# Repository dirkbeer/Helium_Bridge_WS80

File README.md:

# Helium_Bridge_WS80

### Note: This is a specialized version of Helium Bridge for the Ecowitt/Fine Ofsset WS-80 Weather Station. It includes data processing and sleep features to optimize for low-power off-grid use. See the [Helium-Bridge](https://github.com/dirkbeer/Helium-Bridge) repository for the more universal Bridge that can bridge multiple sensors. The PCB design provided there works for both.

This repository contains Helium_Bridge_WS80, an application that bridges sensor signals from industrial, scientific, and medical (ISM) devices to the Helium LoRaWAN network. The code is currently based on https://github.com/lnlp/LMIC-node with additional libraries and code to receive, process, and uplink ISM band data to Helium.

The current code and Helium Bridge hardware receives and uplinks data packets from Ecowitt WS80 weather stations. The WS80 transmits FSK-encoded signals in the sub-1GHz ISM bands (915MHz for US versions). This hardware and code receives, averages, and uplinks WS80 data to Helium.

The Helium Bridge software and PCB design was sponsored by an innovation grant from the [Helium Foundation](https://www.helium.foundation/) to be made available open source. This work is freely available for use under its [MIT License](https://github.com/dirkbeer/Helium-Bridge/blob/main/LICENSE), copyright (c) 2023 Dirk Beer and [Gristle King, Inc](https://gristleking.com/). 

The hardware used includes:

* LILYGO® TTGO LoRa32 V2.1_1.6 https://www.lilygo.cc/products/lora3
* CC1101 433MHz Green Tranceiver Module https://www.ebay.com/itm/311955775989?var=610749871056
* MakerFocus 3.7V Lithium Rechargeable Battery w/ JST1.25 Connector 2pin & Protection Board https://www.amazon.com/gp/product/B07CXNQ3ZR
* Treedix 5V 150mA Polysilicon Solar Panel https://www.amazon.com/gp/product/B0831CMJB9
* uxcell 5-Pin Micro USB Type B Male Connector https://www.amazon.com/gp/product/B014GMP4E4
* Protoboard, pin connectors and sockets, wire

Notes: 
* We used the 433MHz CC1101 module because it has sufficient range to the WS80 (~10m) even when operated at 915MHz, and has much easier-to-use pin connectors than the other available modules.
* The 5V solar panel is connected directly to the LoRa32 boards mirco USB port. Voltage should not exceed 5.8V (maximum for VBUS on the CP2104 chip).
* The https://github.com/merbanan/rtl_433 repository has information on decoding WS80 data packets (and those from many other devices). 

The Helium Bridge in action, data displayed using Uplink Engine (https://uplinkengine.com/) on MeteoScientific (https://meteoscientific.com/).

How to build the hardware:
* TBD

How to run the software:
* TBD. For now, see the original LMIC-node Readme below.

Josef de Beer at SDHGPA wrote much of the code used to receive and process WS80 packets using the TI CC1101 module. 

Copyright (c) 2023 Dirk Beer and Gristle King Inc

---
---
# LMIC-node

One example to rule them all

## Contents

- [1 Introduction](#1-introduction)
  - [1.1 What does it do?](#11-what-does-it-do)
  - [1.2 Implemented features](#12-implemented-features)
  - [1.3 Requirements](#13-requirements)
- [2 Supported Boards](#2-supported-boards)
  - [2.1 LoRa development boards](#21-lora-development-boards)
  - [2.2 Development boards with external SPI LoRa module](#22-development-boards-with-external-spi-lora-module)
- [3 Details](#3-details)
  - [3.1 setup() function](#31-setup-function)
  - [3.2 doWork job](#32-dowork-job)
  - [3.3 processWork() function](#33-processwork-function)
  - [3.4 processDownlink() function](#34-processdownlink-function)
  - [3.5 Uplink messages](#35-uplink-messages)
  - [3.6 Downlink messages](#36-downlink-messages)
    - [3.6.1  Reset-counter downlink command](#361--reset-counter-downlink-command)
  - [3.7 Status information](#37-status-information)
    - [3.7.1 Serial port and display](#371-serial-port-and-display)
    - [3.7.2 LED](#372-led)
  - [3.8 User modifiable code](#38-user-modifiable-code)
  - [3.9 Board-id](#39-board-id)
  - [3.10 Device-id](#310-device-id)
  - [3.11 platformio.ini](#311-platformioini)
  - [3.12 lorawan-keys.h](#312-lorawan-keysh)
  - [3.13 Board Support Files (BSF)](#313-board-support-files-bsf)
  - [3.14 Payload formatters](#314-payload-formatters)
    - [3.14.1 Uplink decoder](#3141-uplink-decoder)
  - [3.15 External libraries](#315-external-libraries)
- [4 Settings](#4-settings)
  - [4.1 Board selection](#41-board-selection)
  - [4.2 Common settings](#42-common-settings)
  - [4.3 LoRaWAN library settings](#43-lorawan-library-settings)
    - [4.3.1 MCCI LoRaWAN LMIC library settings](#431-mcci-lorawan-lmic-library-settings)
    - [4.3.2 IBM LMIC framework settings](#432-ibm-lmic-framework-settings)
  - [4.4 Board specific settings](#44-board-specific-settings)
  - [4.5 Board Support Files](#45-board-support-files)
- [5 Instructions](#5-instructions)
  - [5.1 Select your board](#51-select-your-board)
  - [5.2 Select your LoRaWAN region](#52-select-your-lorawan-region)
  - [5.3 Provide the LoRaWAN keys for your node](#53-provide-the-lorawan-keys-for-your-node)
  - [5.4 Compile and upload](#54-compile-and-upload)
  - [5.5 Add uplink decoder function in TTN Console](#55-add-uplink-decoder-function-in-ttn-console)
- [6 Additional information](#6-additional-information)
  - [6.1 Pinout diagrams](#61-pinout-diagrams)
  - [6.2 The Things Network Forum](#62-the-things-network-forum)
  - [6.3 Not yet tested](#63-not-yet-tested)
  - [6.4 Known issues](#64-known-issues)
- [7 Tips](#7-tips)
  - [7.1 Serial Monitor](#71-serial-monitor)
  - [7.2 Antenna](#72-antenna)
  - [7.3 Distance to gateway](#73-distance-to-gateway)
- [8 Example output](#8-example-output)
  - [8.1 Serial Monitor](#81-serial-monitor)
  - [8.2 Display](#82-display)
- [9 Release History](#9-release-history)

## 1 Introduction

LMIC-node is an example LoRaWAN application for a node that can be used with [The Things Network](https://www.thethingsnetwork.org/). It demonstrates how to send uplink messages,  how to receive downlink messages, how to implement a downlink command and it provides useful status information. With LMIC-node it is easy to get a working node quickly up and running. LMIC-node supports many popular (LoRa) development boards out of the box. It uses the Arduino framework, the LMIC LoRaWAN library and PlatformIO.

Basic steps to get a node up and running with LMIC-node:

- Select a supported board in `platformio.ini`.
- Select your LoRaWAN region in `platformio.ini`.
- Provide the LoRaWAN keys for your node (end device) in `lorawan-keys.h`.
- Compile and upload the firmware and you're ready to go!

### 1.1 What does it do?

- During startup LMIC-node sends some information to the serial port (if enabled) and display (if present and enabled). If OTAA activation is used LMIC-node will explicitly start a join to setup a network session.
- The main work like collecting input data and scheduling uplink messages is performed in the doWork job. This job runs at regular intervals (`DO_WORK_INTERVAL_SECONDS`).
- LMIC-node uses a counter to simulate a real sensor. The counter gets automatically incremented each time its value is read. The counter value is read by the doWork job and then transmitted via an uplink message to The Things Network (TTN).
- In addition LMIC-node also implements a downlink command to reset the counter. The command is sent to the node via a downlink message. When the 'reset counter' command is received by the node it will reset the counter value.
- While all this is happening LMIC-node outputs status information to the serial port for viewing on the serial monitor and also outputs information to the display (if present). The status information will show time, events (e.g. EV_JOINED, EV_TXCOMPLETE), uplink and downlink framecounters, RSSI and SNR of received downlink messages and when a downlink contains data the data will be displayed as bytes.
- The uplink messages can be viewed in the TTN Console. It is also possible to send the 'reset counter' downlink message from the console to the node. The effect of resetting the counter can be watched on the console as arriving uplink messages will show the new counter value.  

Once the node is up and running you can start to explore and customize the source code to your own needs, e.g. add support for sensors. It is always easier to start with something that already works and then continue from there. Have fun!

### 1.2 Implemented features

- Send uplink messages.
- Receive downlink messages.
- Implements a downlink command.
- Provide detailed status feedback via serial port, LED and OLED display.  
*Each of these output channels can be separately enabled/disabled (e.g. to save memory or power).*
- Supports both OTAA and ABP activation. Simply switch via configuration option.
- LoRaWAN keys are placed in a separate file: `lorawan-keys.h`.
  - Protection against accidentally uploading LoRaWAN keys to public Git(Hub) repositories.
  - Easy to swap LoRaWAN keys for testing or for use with multiple devices.
- Requires only some configuration, but no programming or modification of source code to get it up and running.
- Configuration is done in a single project configuration file: `platformio.ini`.
- User modifiable code is clearly marked in the source code.
- Supports two different LMIC libraries: MCCI LoRaWAN LMIC library and IBM LMIC framework.
- Support for many popular (LoRa) development boards.
- Cross-platform, tested on STM32, SAMD21, ESP32, ESP8266, RP2040, MKL26Z64VFT4, ATmega32u4 and ATmega328 boards.
- Hardware dependencies are handled in separate Board Support Files (BSF).
- Built-in 'wait for serial port ready' with adjustable timeout and countdown visible on display. *Useful when using the serial monitor with boards with MCU with integrated USB support.*
- Abstraction of the serial port so code can print to `serial` without needing to know if it must print to `Serial` or `SerialUSB`.
- Use correct GPIO pins for onboard LED, display, LoRa hardware, I2C and SPI ports even if these are incorrectly defined in the BSP.
- Avoid hardware conflicts i.e. GPIO's shared between onboard LED, I2C, SPI and/or Vext.
- Explicitly initialize I2C and SPI interfaces with correct pins if default pins are incorrectly defined in the BSP.
- Select the proper subband for regions US915 and AU915.
- For LMIC debugging, for each board, LMIC_PRINTF_TO is defined for the correct serial port.
*No need to set the `LMIC_PRINTF_TO` parameter to `Serial` or `SerialUSB` manually.*

### 1.3 Requirements

The following is required to use LMIC-node:

- **A supported** LoRa **development board** or development board with external Semtech SX127*x*, HopeRF RFM9*x* or HPDTek HPD1*x*A SPI LoRa module.
- **A computer with [PlatformIO](https://platformio.org/) installed**. PlatformIO is used instead of Arduino IDE because more flexible, more powerful and it better supports cross-platform development. For installation see [PlatformIO installation instructions](https://docs.platformio.org/en/latest/integration/ide/vscode.html).
- **Internet connection**. PlatformIO will automatically download and install packages (Arduino cores, toolchains and libraries) as needed.  
If PlatformIO is freshly installed the downloading may take some time. Once installed it will be possible to work offline.
- **USB cable**. For boards without onboard USB also a **USB to serial adapter** is needed (for STM32 optionally a STLink programmer).
- **Wiring**: Some LoRa development boards require manual wiring of LoRa DIO1 (see table below). When using a development board with external LoRa module then everything must be manually wired. For wiring details see the board's Board Support File (BSF).
- **Node registration**: A node (end device) must be created/registered in The Things Network (TTN) Console before it can be used. The LoRaWAN keys for the device must be copied from the TTN Console to file `lorawan-keys.h`. Registration is not further described here. For more information see [The Things Network documentation](https://www.thethingsnetwork.org/docs/index.html), [The Things Stack documentation](https://www.thethingsindustries.com/docs) and [The Things Network Forum](https://www.thethingsnetwork.org/forum/).
- **Skills**: You should already be familiar with compiling and uploading basic Arduino sketches to your board and how to use a serial monitor.

**Display**:  
LMIC-node supports the following display type: SSD1306 128x64 I2C OLED. These are the displays used on Heltec Wifi LoRa 32 and TTGO LoRa32 boards. When connecting an external display use this type. Use of other I2C displays is possible but requires modification of LMIC-node which is not further described here.

Not yet a requirement but this document assumes that you will be using The Things Network V3 as The Things Network V2 will cease operation by the end of 2021 and should not be used for new development.

## 2 Supported Boards

The following tables list the boards currently supported by LMIC-node.

Explanation of columns: MCU: microcontroller. Wiring required: yes means manual wiring of DIO1 is required. USB: has onboard USB. LED: yes: has onboard LED *and* is usable (no hardware conflicts). Display: yes means has onboard display. Board-id: board identifier as used by LMIC-node.

### 2.1 LoRa development boards

The following LoRa development boards have onboard LoRa support. Most have onboard USB that supports automatic firmware upload and serial over USB for serial monitoring. Some boards require manual wiring of the LoRa DIO1 port. For boards without onboard display an external display can be optionally connected. For details and wiring instructions see the board's BSF.

| Board name                        | MCU               | Wiring required | USB      | LED      | Display   | Board-id |
| ----------                        | ---               | ---             | ---      | ---      | ---       | --- |  
| Adafruit Feather M0 RFMx LoRa     | SAMD21G18         | yes _\*1_       | yes      | yes      | no        | adafruit_feather_m0_lora |
| ST B-L072Z-LRWAN1 Discovery kit   | STM32L072CZ       | no              | yes      | yes      | no        | discovery_l072z_lrwan1 |
| Heltec WiFi LoRa 32 V2            | ESP32             | no              | yes      | yes      | yes       | heltec_wifilora32_v2 |
| Heltec WiFi LoRa 32 (1.x)         | ESP32             | no              | yes      | yes      | yes       | heltec_wifilora32 |
| Heltec Wireless Stick             | ESP32             | no              | yes      | yes      | yes _\*7_ | heltec_wireless_stick |
| Heltec Wireless Stick Lite        | ESP32             | no              | yes      | yes      | no        | heltec_wireless_stick_lite |
| Pycom LoPy4                       | ESP32             | no              | no _\*4_ | no _\*5_ | no        | lopy4 |
| BSFrance LoRa32u4 II<br>*versions v1.0, v1.1, v1.2 and v1.3* | ATmega32u4 | yes _\*2_ | yes | yes | no    | lora32u4II |
| TTGO LoRa32 V1.3                  | ESP32             | no              | yes      | no       | yes       | ttgo_lora32_v1 |
| TTGO LoRa32 V2.0                  | ESP32             | yes _\*3_       | yes      | no _\*6_ | yes       | ttgo_lora32_v2 |
| TTGO LoRa32 V2.1.6                | ESP32             | no              | yes      | no       | yes       | ttgo_lora32_v21 |
| TTGO T-Beam<br>*versions v0.5, v0.6 and v0.7* | ESP32 | no              | yes      | yes      | no        | ttgo_tbeam |
| TTGO T-Beam<br>*versions v1.0 and v1.1*       | ESP32 | no              | yes      | no       | no        | ttgo_tbeam_v1 |

_\*1_: DIO1 must be manually wired to GPIO6.  
_\*2_: For versions 1.0, 1.1 and 1.2 DIO1 must be manually wired to GPIO5 (version 1.3 is already wired on the PCB).  
_\*3_: DIO1 must be manually wired to GPIO33.  
_\*4_: Requires USB to Serial adapter or Pycom Expansion Board which is explained further below.  
_\*5_: Has onboard Neopixel RGB LED but is currently not supported by LMIC-node.  
_\*6_: Either display (I2C) or LED can be used but not both at the same time. LED is default disabled.  
_\*7_: Display (64x32) not supported by LMIC-node because resolution is too small.

### 2.2 Development boards with external SPI LoRa module

The following development boards require an external Semtech SX127*x*, HopeRF RFM9*x* or HPDTek HPD1*x*A SPI LoRa module *(Semtech SX1262 is currently not supported by the LMIC library)*.
Most boards have onboard USB that supports automatic firmware upload and serial over USB for serial monitoring.
An external display can be optionally connected. For details and wiring instructions see the board's BSF.

| Board name                        | MCU            | Wiring required | USB       | LED      | Display | Board-id |
| ----------                        | ---            | ---             | ---       | ---      | ---     | -------- |
| Adafruit QT PY                    | SAMD21E18      | yes             | yes       | no _\*5_ | no      | adafruit_qt_py_m0 |
| Black Pill STM32F103C8 128k       | STM32F103C8T6  | yes             | yes _\*8_ | yes      | no      | blackpill_f103c8_128k |
| Black Pill STM32F103C8 64k        | STM32F103C8T6  | yes             | yes _\*8_ | yes      | no      | blackill_f103c8 |
| Blue Pill STM32F103C8 128k        | STM32F103C8T6  | yes             | yes _\*8_ | yes      | no      | bluepill_f103c8_128k |
| Blue Pill STM32F103C8 64k         | STM32F103C8T6  | yes             | yes _\*8_ | yes      | no      | bluepill_f103c8 |
| Lolin D32 Pro                     | ESP32          | yes             | yes       | yes      | no      | lolin_d32_pro |
| Lolin D32                         | ESP32          | yes             | yes       | yes      | no      | lolin_d32 |
| Lolin32                           | ESP32          | yes             | yes       | yes      | no      | lolin32 |
| NodeMCU-32S                       | ESP32          | yes             | yes       | yes      | no      | nodemcu_32 |
| NodeMCU V2 (aka v1.0)             | ESP8266        | yes             | yes       | yes      | no      | nodemcuv2 |
| Raspberry Pi Pico                 | RP2040         | yes             | yes       | yes      | no      | pico |
| Arduino Pro Mini (ATmega328 8mHz) | ATmega328      | yes             | yes       | no       | no      | pro8mhzatmega328 |
| SAMD21 M0-Mini                    | SAMD21G18      | yes             | yes       | no       | no      | samd21_m0_mini |
| Teensy LC                         | MKL26Z64VFT4   | yes             | yes       | yes      | no      | teensylc |

_\*5_: Has onboard Neopixel RGB LED but is currently not supported by LMIC-node.  
_\*8_: These boards have onboard USB but by default do not support firmware upload over USB or serial over USB. For upload use a STLink programmer or USB to serial adapter.

## 3 Details

This chapter contains detailed information about LMIC-node.

### 3.1 setup() function

During setup the following components and any corresponding libraries are initialized: serial port, display, LED, LoRa pin mappings, I2C, SPI, LMIC. Additionally other hardware like sensors and their libraries can be initialized (LMIC-node uses a counter to simulate a sensor).

The first step in `setup()` is:

```cpp
// boardInit(InitType::Hardware) must be called at start of setup() before anything else.
bool hardwareInitSucceeded = boardInit(InitType::Hardware);
```

The `boardInit()` function is defined in the board's Board Support File.  
If OTAA activation is used then during setup a join will be explicitly started to establish a connection with the network.  
The last step in `setup()` is scheduling the first run of the `doWork` job.

### 3.2 doWork job

The `doWork` job runs every `DO_WORK_INTERVAL_SECONDS`.  
To run the job the `doWorkCallback()` function is executed by the LMIC scheduler.  
`doWorkCallback()` calls the `processWork()` function where the actual work is performed.  
The first `doWork` run is started in `setup()`. On completion `doWork` reschedules itself for the next run.

When the node has joined and the `EV_JOINED` event is handled by the event handler, the next scheduled doWork job is cancelled and is re-scheduled for immediate execution. This is done to prevent that any uplink will have to wait until the current doWork interval ends. `processWork()` skips doing any work while the node is still joining. As a result sending the first uplink message may have to wait until the current doWork interval ends (max `DO_WORK_INTERVAL_SECONDS` seconds). Directly running the doWork job after a join prevents the in this case unnecessary and unwanted delay.

### 3.3 processWork() function

The `processWork()` function contains user code that performs the actual work like reading sensor data and scheduling uplink messages. In LMIC-node `processWork()` will skip doing any work if the node is still joining for two reasons:

1. To prevent unnecessary incrementing of the counter.
2. Uplink messages cannot yet be sent.

### 3.4 processDownlink() function

The `processDownlink()` function contains user code for processing a downlink message.  
`processDownlink()` is called from the event handler function when an EV_TXCOMPLETE event is handled and a downlink message was received.

### 3.5 Uplink messages

The counter is implemented as an unsigned 16 bit integer.
The uplink payload consists of the counter value, 2 bytes in msb format (most significant byte first).
The frame port number used for uplink messages is 10.
Port 10 is used to demonstrate that other port numbers than the default 1 can be used.

### 3.6 Downlink messages

There are two types of downlink messages. Downlink messages containing user data and downlink messages containing MAC commands. MAC commands are sent by the network server to set or query network related settings.

When a downlink message is received its RSSI and SNR values will be displayed as well as the port number. If the port number is 0 and no data is shown then a MAC command was received.

If the port number is greater than 0 and user data was received the data will be displayed as a sequence of byte values. Contents of downlink data will only be output to the serial port and not to the display because the display is too small to fit all information on a single screen.

#### 3.6.1  Reset-counter downlink command

The reset-counter downlink uses 100 as frame port number.
The reset command is represented by a single byte with hex value 0xC0 (for Counter 0).
When a downlink message is received on port 100, the length of the data is 1 byte and the value is 0xC0 then the `resetCounter()` function will be called and the counter will be reset to 0. If the received payload data is longer than a single byte then the reset-counter command will not be performed.

### 3.7 Status information

The following status information is shown:

#### 3.7.1 Serial port and display

At the start:

- Timeout countdown value while waiting for serial port to become ready is shown on the display. This value is only shown for boards where `WAITFOR_SERIAL_SECONDS_DEFAULT` is defined in the BSF with a value unequal to 0.

In the header:

- Program title "LMIC-node".
- Device-id.
- Used LMIC library. MCCI or Classic. On display only an asterisk will be shown if Classic is used.
- If OTAA or ABP activation is used. On display only ABP will be shown if used.
- LMIC debug level if > 0. *(on serial port only)*
- DoWork job time interval (DO_WORK_INTERVAL_SECONDS). On display 'interval' label is abbreviated to "I".

When joined:

- Network-id. *(on serial port only, MCCI LMIC only)*
- Device address. *(on serial port only, MCCI LMIC only)*
- Sessions keys *(son erial port only, MCCI LMIC only)*

Continuously:

- During transmission of uplink and downlink messages a transmit symbol will be shown in the top-right of the display. the transmit symbol and LED are called transmit indicators. For MCCI LMIC transmit indicators are set to on while handling the EV_TXSTART event. Classic LMIC does not generate this event however. For Classic LMIC the transmit indicators will be set to on after an uplink has been successfully scheduled (which is less precise).
- A notification when the doWork job is started. *(on serial port only)*
- A notification when input data was collected *(on serial port only)*
- Message with Counter value. On display label is abbreviated to "Ctr".
- A notification "packet queued" when an uplink message is scheduled.
- A notification if a packet cannot be scheduled because transmission or reception of another message is still pending.
- An error message if scheduling of an uplink message failed.
- Events generated by the LMIC library (e.g. EV_JOINED, EV_TXCOMPLETE).
- When event EV_TXCOMPLETE is received the frame counters are printed.
- For each downlink message the following will be shown:
  - Message that downlink was received
  - RSSI and SNR values
  - Frame port number
  - If data was received, length of data
  - If data was received, the data is shown as as byte *(serial port only)*
  - Message if reset-counter command was received *(serial port only*)
- Notification when counter is reset.

For events and notifications a timestamp (`ostime`) will be shown. LMIC uses values of the type ostime_t to represent time in ticks. The rate of these ticks defaults to 32768 ticks per second (but may be configured at compile time to any value between 10000 ticks per second and 64516 ticks per second).

#### 3.7.2 LED

The LED is a transmit indicator similar to the transmit symbol on the display. For a description when the LED is on and off see the description for the transmit symbol above.

### 3.8 User modifiable code

LMIC-node will work out of the box without having to do any programming or modifying of source code. However, LMIC-node will only do a few tricks: Send counter value via uplink messages, handle reset-counter downlink command and show detailed status information.

To make LMIC-node do other, more useful things e.g. reading values from a temperature and humidity sensor or from a water-level sensor and sending these via uplink messages, requires modifying and extending the source code.

Most of the source code is boiler plate code that does not need to be changed.
Code for things like adding support for sensors or implement other downlink commands is called *User Code*. In `LMIC-node.cpp` three sections in the source code are marked as *User Code*. In `platformio.ini` one section is marked for User Code where additional libraries for User Code can be added. Try to put your user code in these sections (this will prevent accidentally messing things up).

If you are aware of what you are doing you are of course free to change every single line of code to your needs, but if this is new to you it might be safer to restrict modifications to the user code sections.

Reading sensors (etc), preparing uplink payload and scheduling an uplink message for transmission can be done in function `processWork()`. Handling of downlink messages and adding your own downlink commands can be done in function `processDownlink()`.

The User Code sections in `LMIC-node.cpp` are marked as follows:

```cpp
//  █ █ █▀▀ █▀▀ █▀▄   █▀▀ █▀█ █▀▄ █▀▀   █▀▄ █▀▀ █▀▀ ▀█▀ █▀█
//  █ █ ▀▀█ █▀▀ █▀▄   █   █ █ █ █ █▀▀   █▀▄ █▀▀ █ █  █  █ █
//  ▀▀▀ ▀▀▀ ▀▀▀ ▀ ▀   ▀▀▀ ▀▀▀ ▀▀  ▀▀▀   ▀▀  ▀▀▀ ▀▀▀ ▀▀▀ ▀ ▀

const uint8_t payloadBufferLength = 4;    // Adjust to fit max payload length

//  █ █ █▀▀ █▀▀ █▀▄   █▀▀ █▀█ █▀▄ █▀▀   █▀▀ █▀█ █▀▄
//  █ █ ▀▀█ █▀▀ █▀▄   █   █ █ █ █ █▀▀   █▀▀ █ █ █ █
//  ▀▀▀ ▀▀▀ ▀▀▀ ▀ ▀   ▀▀▀ ▀▀▀ ▀▀  ▀▀▀   ▀▀▀ ▀ ▀ ▀▀
```

The User code section in `platformio.ini` is marked as follows:

```ini
;   ███ Add additional libraries for User Code below this line ███
```

Names of libraries needed for User Code can be specified below above line.

### 3.9 Board-id

LMIC-node uses a _board-id_ to identify a specific type of board. _board-id_ is similar to PlatformIO's _board_ but latter is limited to BSP's defined in Arduino cores. Unfortunately there does not exist a dedicated BSP for each board supported by LMIC-node. Therefore LMIC-node defines its own board identifiers.

_board-id_ is kept identical or as similar as possible to PlatformIO's _board_. For simplicity and consistency _board-id_ only uses underscores and lowercase characters (e.g. `heltec_wifi_lora_32_v2` and `ttgo_lora32_v2`) while PlatformIO's _board_ uses hyphens, underscores and mixed case characters (e.g. `heltec_wifi_lora_32_V2` and `ttgo-lora32-v2`). Board-id `lora32u4II` is an exception, the `II` is uppercase because it is a Roman numeral.  

 If a proper _board_ definition and BSP for some version of a development board do currently not exist then LMIC-node defines its own board with its own _board-id_. In which case it will use the closest matching _board_ in PlatformIO and add a separate BSF for _board-id_ where the differences can be properly handled. In this case _board-id_ will be the same as _board_ but suffixed with a version e.g. `ttgo_t_beam_v1`. In this example there only exists a board `ttgo-t-beam` in PlatformIO but no `ttgo-t-beam-v1` while there are important hardware differences between v0.x and v1.x versions of these boards.

### 3.10 Device-id

LMIC-node uses a device-id to identify a device. The device-id is used for display purposes in status information that is output to the serial port and display. Device-id's allow different devices to be easily recognized when they have different device-id's, because their device-id is shown on the display (if present) and/or serial monitor (serial port). The length of a device-id should be limited to max 16 characters long, otherwise it will not fit on a display.

When creating a device in the TTN console one must specify a unique device identifier for the device. The device-id used in LMIC-node is only used for display purposes (and is not the same as the device identifier in the TTN Console) but it is useful to use the same device-id for LMIC-node as the device identifier in the TTN console (or at least make it similar). That will make it easier to recognize traffic in the TTN console because the device identifier displayed on the console and the device-id displayed on the node's display (or serial monitor) will match.

In the BSF a default device-id (`DEVICEID_DEFAULT`) is defined per board type. The default device-id can be overriden by defining `DEVICEID` in file `lorawan-keys.h`, or defining `ABP_DEVICEID` in `lorawan-keys.h`. If defined latter will be used when ABP activation is used.

`lorawan-keys.h` can contain both the keys used for OTAA activation as well as the keys used for ABP activation. Keys used for OTAA and ABP are different and they have different names. Only the keys for the used actvation type (OTAA or ABP) need to be specified.

Tip: For testing purposes it is possible to create two different devices in the TTN console for the same hardware device, one for OTAA activation and the other for ABP activation. Both sets of keys can be added to lorawan-keys.h and for both a different device-id can be added to lorawan-keys.h. This way a single hardware device can be used for both OTAA and ABP (only one at a time). All that to needs to be done to switch the device from OTAA to ABP is to enable the `-D ABP_ACTIVATION` setting in the `[common]` section in `platformio.ini` (or vice versa) and then recompile and upload the firmware.

### 3.11 platformio.ini

`platformio.ini` is the project configuration file. This file contains all configuration settings like program options, names of libraries and build options. It contains below sections:

- **[platformio]**  
  Contains a list of board names and their corresponding board-id ('environment definitions').  
  This is used to select a board (by uncommenting the line with the board-id to be selected).

- **[common]**  
  Contains settings used for all boards.

- **[mcci_lmic]**  
  Contains MCCI LoRaWAN LMIC library specific settings.  
  MCCI LoRaWAN LMIC library is used for boards with 32-bit MCU.

- **[classic_lmic]**  
  Contains IBM LMIC framework library specific settings.  
  IBM LMIC framework is used for boards with 8-bit AVR MCU.  
  These boards have less available memory and Classic LMIC uses less memory resources than MCCI LMIC.  
  It is not possible to use LMIC-node with MCCI LMIC on these boards due to insufficient memory.  
**Be aware that Classic LMIC is not fully LoRaWAN compliant and should not be used with ABP activation on The Things Network V3. IBM LMIC framework (Clasic LMIC) was recently deprecated and is not further maintained.**

- **[env:_\<board-id\>_]**  
  Board specific sections (called _Environments_ in PlatformIO terminology). E.g. [env:lolin32]. A board specific section contains settings that are specific for one type of board.   It contain settings like which LMIC library to use and program options like USE_SERIAL, USE_LED and USE_DISPLAY.  

Comments in platformio.ini start with a semicolon ( ; ) character. To uncomment a line  remove the semicolon prefix. To comment a line add a semicolon prefix.

### 3.12 lorawan-keys.h

File `lorawan-keys.h` contains the LoRaWAN keys for a node. The keys are placed in a separate file for:

- Protection against accidentally uploading LoRaWAN keys to public Git(Hub) repositories.
- Prevent that source code needs to be modified for changing keys.
- Make it easy to swap LoRaWAN keys for testing purposes or for use with multiple devices.

The keys use three different formats (lsb, msb and uint32_t). lsb: least significant byte, msb: most significant byte. The TTN console provides options to copy keys in different formats. Use the correct formats as shown in below extract from `lorawan-keys_example.h`:

```cpp
// Optional: If DEVICEID is defined it will be used instead of the default defined in the BSF.
// #define DEVICEID "<deviceid>"

// Keys required for OTAA activation:

// End-device Identifier (u1_t[8]) in lsb format
#define OTAA_DEVEUI 0x00, 0x00, 0x00, 0x00, 0x00, 0x00, 0x00, 0x00

// Application Identifier (u1_t[8]) in lsb format
#define OTAA_APPEUI 0x00, 0x00, 0x00, 0x00, 0x00, 0x00, 0x00, 0x00

// Application Key (u1_t[16]) in msb format
#define OTAA_APPKEY 0x00, 0x00, 0x00, 0x00, 0x00, 0x00, 0x00, 0x00, 0x00, 0x00, 0x00, 0x00, 0x00, 0x00, 0x00, 0x00

// -----------------------------------------------------------------------------

// Optional: If ABP_DEVICEID is defined it will be used for ABP instead of the default defined in the BSF.
// #define ABP_DEVICEID "<abp-deviceid>"

// Keys required for ABP activation:

// End-device Address (u4_t) in uint32_t format. 
// Note: The value must start with 0x (current version of TTN Console does not provide this).
#define ABP_DEVADDR 0x00000000

// Network Session Key (u1_t[16]) in msb format
#define ABP_NWKSKEY 0x00, 0x00, 0x00, 0x00, 0x00, 0x00, 0x00, 0x00, 0x00, 0x00, 0x00, 0x00, 0x00, 0x00, 0x00, 0x00

// Application Session K (u1_t[16]) in msb format
#define ABP_APPSKEY 0x00, 0x00, 0x00, 0x00, 0x00, 0x00, 0x00, 0x00, 0x00, 0x00, 0x00, 0x00, 0x00, 0x00, 0x00, 0x00

```

The `lorawan-keys.h` file is located in folder `keyfiles`.

All files with name pattern `*lorawan-keys.h` and all files in folder `keyfiles` (except for file `lorawan-keys_example.h`) are excluded from the Git(Hub) repository (defined in file `.gitignore`) to prevent that LoRaWAN keys will be accidentally committed to a public repository.

`lorawan-keys_example.h` is included as example for `lorawan-keys.h`.

### 3.13 Board Support Files (BSF)

A Board Support File (BSF) isolates hardware dependencies for a board into a single file: the BSF. There is a separate BSF per board type.  

A Board Support Package (BSP) provides support for a specific board and provides standard pin definitions for a board. BSP's are part of an Arduino core, which contains a BSP for each supported board.  

A BSF acts like a mini Board Support Package (BSP). A BSF adds functionality on top of the BSP and can also contain corrections if pins are incorrectly defined in the BSP.  

A BSF has the same name as the board-id, is prefixed with `bsf_` and suffixed with `.h` extension. BSF's are located in the `src/boards` folder.  
Exceptions:

- `lora32u4II` the `II` is uppercase because it is a Roman numeral.
- `blackpill_f103c8_128k` and `bluepill_f103c8_128k` use the same BSF as their 64k versions.

A BSF contains important information about a board (including connection/wiring details), contains a URL to PlatformIO's documentation for the board and provides the following functionality:

- Defines the default device-id.
- Defines 'wait for serial port' timeout default value (if needed).
- Defines if LMIC timing should be relaxed (if needed).
- Defines a reference named `serial` that points to the correct serial port (Serial or SerialUSB).
- Defines and initializes the `led` object.
- Defines the `display` object.
- Defines the `lmic_pins` pin mapping structure used by the LMIC library.
- Contains the `boardInit()` function.
- Uses correct GPIO pins for onboard LED, display, LoRa hardware, I2C and SPI ports even if these are incorrectly defined in the BSP in the Arduino core.
- Avoids hardware conflicts i.e. GPIO's shared between onboard LED, I2C, SPI and/or Vext.

The `boardInit(initType)` function provides a generic mechanism for performing custom hardware initialization. It is called twice during setup(). The `initType` parameter indicates which initialization code must be executed.

- `InitType::Hardware`:
  - Explicitly initializes I2C and SPI interfaces with correct pins if default pins are incorrectly defined in the BSP (if needed).
  - Special hardware initialization (if needed, e.g. initializing T-Beam v1.x power management chip).

- `InitType::PostInitSerial`:
  - Inserts a delay after serial port initialization to prevent losing the first output printed to the serial port (if needed).

Example of the `boardInit()` function for a board that does not require custom hardware initialization:

```cpp
bool boardInit(InitType initType)
{
    // This function is used to perform board specific initializations.
    // Required as part of standard template.

    // InitType::Hardware        Must be called at start of setup() before anything else.
    // InitType::PostInitSerial  Must be called after initSerial() before other initializations.    

    bool success = true;
    switch (initType)
    {
        case InitType::Hardware:
            // Note: Serial port and display are not yet initialized and cannot be used use here.
            // No actions required for this board.
            break;

        case InitType::PostInitSerial:
            // Note: If enabled Serial port and display are already initialized here.
            // No actions required for this board.
            break;           
    }
    return success;
}
```

### 3.14 Payload formatters

Payload formatter functions are located in the `payload-formatters` folder.

#### 3.14.1 Uplink decoder

LMIC-node comes with a JavaScript payload formatter function for decoding the uplink messages so the counter value gets displayed in 'Live data' on the TTN Console. The `decodeUplink()` function can be found in folder `payload-formatters` in file `lmic-node-uplink-formatters.js`.

```js
function decodeUplink(input) {
    var data = {};
    var warnings = [];

    if (input.fPort == 10) {
        data.counter = (input.bytes[0] << 8) + input.bytes[1];
    }
    else {
        warnings.push("Unsupported fPort");
    }
    return {
        data: data,
        warnings: warnings
    };
}
```

In the TTN Console this function should be added to the device (or application) as uplink payload formatter function.
When this function is installed, the counter value will become visible in uplink messages in 'Live data' on the TTN Console.

### 3.15 External libraries

LMIC-node uses the following external libraries:

| Library name | Category | Repository URL |
| --- | --- | --- |
| MCCI LoRaWAN LMIC library | LoRaWAN | [https://github.com/mcci-catena/arduino-lmic](https://github.com/mcci-catena/arduino-lmic) |
| IBM LMIC framework | LoRaWAN | [https://github.com/matthijskooijman/arduino-lmic](https://github.com/matthijskooijman/arduino-lmic) |
| U8g2 | Display | [https://github.com/olikraus/u8g2](https://github.com/olikraus/u8g2) |
| EasyLed | LED | [https://github.com/lnlp/EasyLed](https://github.com/lnlp/EasyLed) |

## 4 Settings

### 4.1 Board selection

In platformio.ini the board must be selected. Select only a single board by uncommenting the line with its board-id. Comment the line starting with "\<platformio.ini board selector guard\>". The guard is explicitly added to prevent that PlatformIO will compile LMIC-node for ALL listed boards, when no board is selected.

Warnings:

- When the guard is disabled and no board is selected then PlatformIO will compile for ALL listed boards!
- The Serial Monitor can only be started when a board has been selected in `platformio.ini`.

```ini
[platformio]
default_envs = 
    <platformio.ini board selector guard> Comment this line and uncomment one board-id below:

    ; LoRa development boards with integrated LoRa support:

    ; Board-id                            Board name
    ;---------                            ----------
    ; adafruit_feather_m0_lora          ; Adafruit Feather M0 LoRa
    ; disco_l072cz_lrwan1               ; Discovery B-L072Z-LRWAN1
    ; heltec_wifi_lora_32_v2            ; Heltec Wifi LoRa 32 V2
    ; heltec_wifi_lora_32               ; Heltec Wifi LoRa 32
    ; heltec_wireless_stick_lite        ; Heltec Wireless Stick Lite
    ; heltec_wireless_stick             ; Heltec Wireless Stick
    ; lopy4                             ; Pycom Lopy4
    ; lora32u4II                        ; BSFrance LoRa32u4 II v1.0, v1.1, v1.2, v1.3
    ; ttgo_lora32_v1                    ; TTGO LoRa32 v1.3
    ; ttgo_lora32_v2                    ; TTGO LoRa32 v2.0
    ; ttgo_lora32_v21                   ; TTGO LoRa32 v2.1.6
    ; ttgo_t_beam                       ; TTGO T-Beam v0.5, v0.6, v0.7
    ; ttgo_t_beam_v1                    ; TTGO T-Beam v1.0, v1.1

    ; Development boards that require an external SPI LoRa module:

    ; Board-id                            Board name
    ;---------                            ----------
    ; adafruit_qt_py_m0                 ; Adafruit QT Py    
    ; blackpill_f103c8_128k             ; Black Pill 128k
    ; blackpill_f103c8                  ; Black Pill  64k
    ; bluepill_f103c8_128k              ; Blue Pill 128k
    ; bluepill_f103c8                   ; Blue Pill  64k
    ; lolin_d32_pro                     ; Lolin D32 Pro
    ; lolin_d32                         ; Lolin D32
    ; lolin32                           ; Lolin32
    ; nodemcu_32s                       ; NodeMCU-32S
    ; nodemcuv2                         ; NodeMCU V2
    ; pico                              ; Raspberry Pi Pico
    ; pro8mhzatmega328                  ; Arduino Pro Mini 3.3V 8Mhz
    ; samd21_m0_mini                    ; SAMD21 M0-Mini
    ; teensylc                          ; Teensy LC
```

### 4.2 Common settings

```ini
[common]

monitor_speed = 115200

build_flags =
    -D DO_WORK_INTERVAL_SECONDS=60

    ; -D ABP_ACTIVATION                ; Use ABP instead of OTAA activation
    ;
    ; -D WAITFOR_SERIAL_SECONDS=10     ; Can be used to override the default value (10)
    ;                                    Only used for boards with default set to != 0 in BSF
    ;
    ; -D STM32_POST_INITSERIAL_DELAY_MS=1500  ; Workaround for STM32 boards. Can be used 
    ;                                           to override value (milliseconds) in BSF

lib_deps =
    olikraus/U8g2                      ; OLED display library
    lnlp/EasyLed                       ; LED library
;   ███ Add additional libraries for User Code below this line ███
```

**monitor_speed**  
Sets the monitor speed for the serial port. 115200 bps should be fine for most purposes and does not need to be changed.

**DO_WORK_INTERVAL_SECONDS**  
Defines the interval for when the doWork job runs where the actual work is done.
Be aware that this is also the interval that uplink messages will be sent. The interval should not exceed TTN's fair use policy and regulatory constraints.

**ABP_ACTIVATION**  
If enabled will use ABP activation instead of OTAA activation (default).

**WAITFOR_SERIAL_SECONDS**  
Can be used to overrule the default value defined in BSF for testing purposes but normally not needed to change this. This setting only has effect for boards where a default value (>0) is already defined and will not have effect for other boards.
'Wait for serial' only is useful when USB functionality is provided by the MCU.

A 'wait for serial' delay of 10 seconds is configured by default in boards where USB support is integrated into the MCU (instead of using onboard USB to serial).
Waiting until the serial (over USB) port is actually ready (via 'wait for serial') prevents the first output printed to the serial port getting lost.

A positive value will wait with a countdown delay (visible on display) for the number of seconds specified. A value of 0 will not wait. A value of -1 will wait indefinitely.

Be aware that the serial port must not only be ready but also a serial monitor needs to be connected. The countdown gives some time to start the serial monitor if not already started. A timeout value prevents that the node waits indefinitely if not connected to a computer. It will continue when the countdown ends.

**STM32_POST_INITSERIAL_DELAY_MS**
For STM32 boards a delay is inserted after initializing the serial port. This is a workaround to prevent that the first output send to the serial port gets lost.
This value is defined in STM32 boards BSF but can be overridden in platformio.ini (the override option was added for testing purposes).

### 4.3 LoRaWAN library settings

#### 4.3.1 MCCI LoRaWAN LMIC library settings

```ini
[mcci_lmic]
; LMIC-node was tested with MCCI LoRaWAN LMIC library v3.3.0.
; Some changes have been announced for future versions of the MCCI library
; which may be incompatible with LMIC-node. In case of problems just
; use mcci-catena/MCCI LoRaWAN LMIC library@3.3.0 below which will
; explicitly use v3.3.0 of the library.
; Perform PlatformIO: Clean after changing library version and
; in case of issues remove the old version from .pio/libdeps/*.

; Note: LMIC_PRINTF_TO is defined for each board separately
;       in the board specific sections. Don't define it in this section.

lib_deps =
    ; Only ONE of below LMIC libraries should be enabled.
    mcci-catena/MCCI LoRaWAN LMIC library           ; MCCI LMIC library (latest release)
    ; mcci-catena/MCCI LoRaWAN LMIC library@3.3.0   ; MCCI LMIC library v3.3.0

build_flags =
    ; Use platformio.ini for settings instead lmic_project_config.h.
    -D ARDUINO_LMIC_PROJECT_CONFIG_H_SUPPRESS

    ; Ping and beacons not supported for class A, disable to save memory.
    -D DISABLE_PING
    -D DISABLE_BEACONS

    ; -D LMIC_DEBUG_LEVEL=1            ; 0, 1 or 2
    
    ; -D CFG_sx1272_radio=1            ; Use for SX1272 radio
    -D CFG_sx1276_radio=1              ; Use for SX1276 radio
    -D USE_ORIGINAL_AES                ; Faster but larger, see docs
    ; -D LMIC_USE_INTERRUPTS           ; Not tested or supported on many platforms
    ; -D LMIC_ENABLE_DeviceTimeReq=1   ; Network time support

    ; --- Regional settings -----
    ; Enable only one of the following regions:    
    ; -D CFG_as923=1
    ; -D CFG_as923jp=1   
    ; -D CFG_au915=1
    ; -D CFG_cn490=1                   ; Not yet supported
    ; -D CFG_cn783=1                   ; Not yet supported
    ; -D CFG_eu433=1                   ; Not yet supported
    -D CFG_eu868=1
    ; -D CFG_in866=1
    ; -D CFG_kr920=1
    ; -D CFG_us915=1
```

**Regional setting**  
--- Regional settings --- is where the regional setting needs to be selected.
Uncomment the line with the appropriate region setting (and comment the other region settings). Only one region may be selected. By default CFG_eu868 (Europe) is selected.

**LMIC_DEBUG_LEVEL**  
This can be uncommented to allow debug information from the LMIC library to be printed.
Possible values are 0, 1, 2 and 3 where 0 provides no debugging information and 3 provides the most information.  
Be aware that enabling debug will increase memory requirements.

Other settings are listed for information but are not further explained here.
For more information see the MCCI LoRaWAN LMIC library documentation.

#### 4.3.2 IBM LMIC framework settings

```ini
[classic_lmic]    
; IMPORTANT:
; This library was recently DEPRECATED and is no longer maintained.
; It is not fully LoRaWAN compliant (e.g. in handling of MAC commands)
; and is therefore less suitable for use with The Things Network V3.
;
; Region, radio and debug settings CANNOT be changed in platformio.ini.
; They must be configured in file: config.h in the following location:
; .pio/libdeps/<board-id>/IBM LMIC framework/src/lmic
;
; When making changes to config.h: 
; CONFIG.H MUST BE CHANGED FOR EACH BOARD SEPARATELY!
; (By default libraries are installed per project per build config/board.)

lib_deps =
    matthijskooijman/IBM LMIC framework   ; [Deprecated] Classic LMIC library

build_flags =
    ; DEFAULT VALUES defined in config.h:
    ; CFG_sx1276_radio 1
    ; CFG_eu868 1
    ; LMIC_DEBUG_LEVEL 0 

    ; Ping and beacons not supported for class A, disable to save memory.
    -D DISABLE_PING
    -D DISABLE_BEACONS
```

**Region, radio and debug settings CANNOT be changed in `platformio.ini`.**  
**When making changes to `config.h` these must be changed separately per board!**  
File `config.h` is located in these folders: `.pio/libdeps/<board-id>/IBM LMIC framework/src/lmic`

Above settings cannot be changed in platformio.ini because they are defined in config.h in the library source code. The settings must be changed separately per board because PlatformIO downloads libraries separately for each board.

**Do NOT use ABP activation when using the IBM LMIC framework library.  
On The Things Network V3 this will cause a downlink message for EVERY uplink message because it does NOT properly handle MAC commands.**

### 4.4 Board specific settings

All options listed below are specified for each board separately. This is done for flexibility and to provide the optimum configuration for each board out of the box.

Example board section for BSFrance LoRa32u4 II board:

```ini
[env:lora32u4II]
; BSFrance LoRa32u4 II V1.0, V1.1, V1.2, V1.3 (ATmega32u4).
; No display.
; Board versions V1.0 to V1.2 require manual wiring of DIO1 to GPIO5.
; 8-bit AVR MCU with limited memory, therefore Classic LMIC is used.
; See limitations described in the [classic_lmic] section.
platform = atmelavr
board = lora32u4II
framework = arduino
monitor_speed = ${common.monitor_speed}  
lib_deps =
    ${common.lib_deps}  
    ${classic_lmic.lib_deps}     ; [Deprecated] IBM LMIC Framework
build_flags =
    ${common.build_flags}
    ${classic_lmic.build_flags}  ; [Deprecated] IBM LMIC Framework
    -D BSFILE=\"boards/bsf_lora32u4II.h\"
    -D MONITOR_SPEED=${common.monitor_speed}
    -D USE_SERIAL
    -D USE_LED
    ; -D USE_DISPLAY             ; Requires external I2C OLED display
```

Example board section for Blue Pill board with external LoRa module:

```ini
[env:bluepill_f103c8]
; Bluepill F103C8 (64k) (STMF103C8T6).
; No display.
; Select preferred upload protocol below.
platform = ststm32
board = bluepill_f103c8
framework = arduino
; upload_protocol = serial
upload_protocol = stlink
; upload_protocol = jlink
monitor_speed = ${common.monitor_speed}    
lib_deps =
    ${common.lib_deps}    
    ${mcci_lmic.lib_deps}
build_flags =
    ${common.build_flags}
    ${mcci_lmic.build_flags} 
    -D BSFILE=\"boards/bsf_bluepill_f103c8.h\"
    -D MONITOR_SPEED=${common.monitor_speed}
    -D _GNU_SOURCE    
    -D LMIC_PRINTF_TO=Serial    
    -D USE_SERIAL
    -D USE_LED
    ; -D USE_DISPLAY             ; Requires external I2C OLED display
```

By default all USE\_ options for a board are enabled. If the option is not enabled by default then it is either not supported (e.g. due to hardware conflict) or in case of USE_DISPLAY requires an external display to be connected. In latter case the USE_DISPLAY option can be enabled after an external display is connected.

Each of these options uses memory. In case of memory constrainted 8-bit boards disabling some of these option may free some memory for other use.

**USE_SERIAL**  
If enabled status output will be send to the serial port to be viewed on serial monitor.

**USE_LED**  
If enabled it will use the onboard LED. The LED will be on during Tx/Rx transmission and off otherwise. For some boards the onboard LED cannot be used because of a hardware conflict, because the LED type is not supported (e.g. WS2812 RGB LED) or because there is no onboard user LED. If the onboard LED cannot be used then this option is disabled by default and the line will be commented to make this clear.

**USE_DISPLAY**  
If enabled status output will be send to the display.

**upload_protocol**  
For some boards it may be necessary to change the upload protocol, e.g. for bluepill change it from `stlink` to `serial` if a USB to serial adapter is used for upload instead of a STLink programmer.

**LMIC library**  
By default all boards with 32-bit MCU are configured to use the MCCI LoRaWAN LMIC library (MCCI LMIC) because this is the library that should be used. It is the most LoRaWAN compliant LMIC library for Arduino and it is actively maintained.  

 By default all boards with 8-bit MCU are configured to use the IBM LMIC framework library (Classic LMIC). These boards have limited memory capacity and Classic LMIC uses less memory than MCCI LMIC. Because of better LoRaWAN compliance and improved functionality MCCI LMIC is preferred but there is not enough memory to use LMIC-node with MCCI LMIC on these boards.

The other entries in the board sections should stay unchanged.

### 4.5 Board Support Files

Each BSF contains the following settings. Except for DEVICEID_DEFAULT these settings are not enabled for each board. Values shown are examples.

```cpp
#define DEVICEID_DEFAULT "pro-mini"  // Default deviceid value

// Wait for Serial
// Can be useful for boards with MCU with integrated USB support.
#define WAITFOR_SERIAL_SECONDS_DEFAULT 10   // -1 waits indefinitely  

// LMIC Clock Error
// This is only needed for slower 8-bit MCUs (e.g. 8MHz ATmega328 and ATmega32u4).
// Value is defined in parts per million (of MAX_CLOCK_ERROR).
// Value 30000 was determined empirically.
#define LMIC_CLOCK_ERROR_PPM 30000
```

**DEVICEID_DEFAULT**  
If no `DEVICEID` is defined and no `ABP_DEVICEID` is defined when ABP activation is used then `DEVICEID_DEFAULT` is used.  
There is no need to change this value in the BSF. `DEVICEID` and `ABP_DEVICEID` can be defined in file `lorawan-keys.h` where they are kept nicely together with the LoRaWAN keys of the same device.

**WAITFOR_SERIAL_SECONDS_DEFAULT**  
Defines the default value used for the 'wait for serial' timeout. This value is only defined in the BSF for boards where USB support is integrated into the MCU. It has no use for other boards.  
If there is need to change this value then don't change the default value in the BSF and change `WAITFOR_SERIAL_SECONDS` in the `[common]` section in `platformio.ini` instead.

**LMIC_CLOCK_ERROR_PPM**  
Setting this value will cause LMIC timing to be less strict. This is only needed for some boards (usually 8-bit AVR based boards). This value should normally not be changed especially for 32-bit MCU boards.  
If there are any issues with timing then increasing this value could possibly help. All boards supported by LMIC-node have already been tested and for boards that need it LMIC_CLOCK_ERROR_PPM is already enabled with a value that has proven to be sufficient.

For more information about Clock Error consult the MCCI LoRaWAN LMIC library documentation.

## 5 Instructions

For prerequisites see [1.3 Requirements](#13-requirements)

### 5.1 Select your board

In `platformio.ini`:

**Step 1a**: Select exactly one supported board by uncommenting the line with its board-id and name.

**Step 1b**: Comment the guard line to disable it. This is the line that starts with `<platformio.ini board selector guard>`.

### 5.2 Select your LoRaWAN region

For MCCI LMIC (default for 32-bit boards):  
**Step 2:** In `platformio.ini` select you LoRaWAN region.  
or  
For Classic LMIC (default for 8-bit boards):  
**Step 2**: In `config.h` select your LoRaWAN region (if not CFG_eu868). See [IBM LMIC framework settings](#432-ibm-lmic-framework-settings) for details.

*If you are not sure which of the above to select then check the section for your board in `platformio.ini`.*

### 5.3 Provide the LoRaWAN keys for your node

**Step 3a**: If this is the first time: In the `keyfiles` folder copy file `lorawan-keys_example.h` to `lorawan-keys.h`.

**Step 3b**: In file `lorawan-keys.h` add the LoRaWAN keys for the device that were copied from the TTN Console.

**Step 3c**: Optional: if preferred, set values for `DEVICEID` and `ABP_DEVICEID` in `lorawan-keys.h` (otherwise default value will be used).

### 5.4 Compile and upload

**Step 4a**: Compile the code.

**Step 4b**: Start the serial monitor (if USE_SERIAL is enabled).

**Step 4c**: Upload the code (and manually reset the device if needed).

**Your node should now be up and running.**

The node will be running but to be able to see the counter value in uplink messages displayed on the console, an uplink decoder function needs to be installed (see next step).

### 5.5 Add uplink decoder function in TTN Console

**Step 5**: In the TTN Console, add the `decodeUplink()` JavaScript function as uplink payload formatter to the device. As formatter type select `JavaScript` and the function must be pasted in the field `Formatter parameter`.

The `decodeUplink()` function can be found in folder `payload-formatters` in file `lmic-node-uplink-formatters.js`.

When this function is installed, the counter value will be shown in uplink messages in 'Live data' on the TTN Console.

## 6 Additional information

### 6.1 Pinout diagrams

Pinout diagrams for most supported boards can be found here: [https://github.com/lnlp/pinout-diagrams](https://github.com/lnlp/pinout-diagrams)

### 6.2 The Things Network Forum

The following topics on The Things Network Forum contain useful additional information:

- [Big ESP32 SX127x topic part 3](https://www.thethingsnetwork.org/forum/t/big-esp32-sx127x-topic-part-3/18436)
- [TTGO T-Beam](https://www.thethingsnetwork.org/forum/t/ttgo-t-beam/15297)
- [Big STM32 boards topic](https://www.thethingsnetwork.org/forum/t/big-stm32-boards-topic/13391)
- [Big LoRa32u4 boards topic](https://www.thethingsnetwork.org/forum/t/big-lora32u4-boards-topic/15273)

### 6.3 Not yet tested

All supported boards have been tested except below boards for which hardware was not available. 

- Heltec Wireless Stick and Wireless Stick Lite.
- BSFrance LoRa32u4 II v1.1 and v1.3 *(v1.0 and v1.2 were tested)*.
- TTGO LoRa32 v1.3.
- TTGO LoRa32 v2.1.6.  
- Lolin D32 *(Lolin D32 Pro was tested)*.

### 6.4 Known issues

There are no known issues in this release.

## 7 Tips

### 7.1 Serial Monitor

If a development board has a MCU with built-in USB support (e.g. ATmega32u4 and SAMD21) and the serial monitor is connected, resetting the board (e.g. with onboard reset button) will temporarily disconnect the serial port and crash the serial monitor. The serial monitor will then have to be manually restarted and the output will be lost. For boards that use a USB to serial adapter (either onboard or external) this problem does not exist.

To prevent issues with the serial monitor it is best to start the serial monitor _before_ uploading a new sketch. After uploading, PlatformIO will automatically switch back from the upload window to the serial monitor and the serial monitor will contine without crashing. If you connect the serial monitor after uploading you will most probably lose the first output, in which case you may be tempted to press the reset button to restart the output, but in case of MCU with built-in USB support this will only crash the serial monitor.

For boards with MCU with built-in USB support LMIC-node by default waits with a 10 seconds timeout for the serial port to become ready so the first output does not get lost. If not yet connected the serial monitor needs to be connected (or restarted) within these 10 seconds. The countdown stops when the serial port becomes ready or when the countdown ends (whichever is first). The value of the countdown period can be changed as needed by enabling and changing the value of (`WAITFOR_SERIAL_SECONDS` in `platformio.ini`). A value 0 will disable the 'wait for serial' countdown, a value of -1 will wait indefinitely and not contiunue until the serial port is ready. The serial port is detected as ready only when a serial monitor is connected.

### 7.2 Antenna

- **The antenna should always be connected when the device is powered!**  
  Powering the board with antenna disconnected may damage the LoRa radio.  

- For best results the antenna should be used in upright (vertical) position.

### 7.3 Distance to gateway

- The distance between the node and a gateway should be 3 meters at minimum. If the distance is less than 3 meters this can cause RF communication issues.

## 8 Example output

Below are some examples of status output from serial monitor and display.

### 8.1 Serial Monitor

Example output from Raspberry Pi Pico with RFM95 SPI LoRa module.  
This is the first serial output after reset. It shows a join, the first two uplinks, then an uplink followed by a downlink containing a counter reset command, and then the next uplink where it is visible that the counter value has been reset. After the third uplink it shows that two downlinks have been received. One was for the reset counter command, the other downlink was for a MAC command that cannot be output because the sequence of up and downlinks all occur before the EV_TXCOMPLETE event is generated.

```text
LMIC-node

Device-id:     rpi-pico  
LMIC library:  MCCI      
Activation:    OTAA      
Interval:      60 seconds

000000087328:  Event: EV_JOINING 

000000088779:  doWork job started
000000115173:  Event: EV_TXSTART
000000437671:  Event: EV_JOINED
               Network Id: 19
               Device Address: 260B9BA3
               Application Session Key: BD-40-9E-1F-9C-36-BC-1C-0F-ED-A9-4C-90-27-84-8A
               Network Session Key:     80-FC-6E-99-9C-67-63-3F-4D-61-70-E1-2C-1D-D6-8E

000003838779:  doWork job started
000003841831:  Input data collected
               COUNTER value: 1    
000003842567:  Packet queued
000003844154:  Event: EV_TXSTART
000004225330:  Event: EV_TXCOMPLETE
               Up: 1,  Down: 0     

000007588779:  doWork job started
000007591830:  Input data collected
               COUNTER value: 2    
000007592585:  Packet queued
000007594181:  Event: EV_TXSTART
000007975350:  Event: EV_TXCOMPLETE
               Up: 2,  Down: 0     

000011338779:  doWork job started
000011341830:  Input data collected
               COUNTER value: 3    
000011342539:  Packet queued
000011344159:  Event: EV_TXSTART
000011725339:  Event: EV_TXCOMPLETE
               Up: 3,  Down: 0     

000015088780:  doWork job started
000015091771:  Input data collected
               COUNTER value: 4    
000015092467:  Packet queued
000015094084:  Event: EV_TXSTART
000015413725:  Event: EV_TXCOMPLETE
               Up: 4,  Down: 2
               Downlink received
               RSSI: -68 dBm,  SNR: 7.2 dB
               Port: 100
               Length: 1
               Data: C0
               Reset cmd received
000015417949:  Counter reset

000018838781:  doWork job started
000018841831:  Input data collected
               COUNTER value: 1    
000018842563:  Packet queued
000018844177:  Event: EV_TXSTART
000019225356:  Event: EV_TXCOMPLETE
               Up: 5,  Down: 2     
```

### 8.2 Display

To be added.

## 9 Release History

**Release v1.3.0**

- Added
  - Separate LMIC_PRINTF_TO definitions for each board that uses MCCI LMIC.
  - Subband selection for US915 and AU915 for OTAA (fixes issue for AU915).
  - Parameterization for `initLmic()` and `setAbpParameters()`.
  - Custom event handler for MCCI LMIC to capture `EV_RXSTART`.
  - User code markers in `setup()`.
  - Description for `setup()`, `processWork()` and `processDownlink()` functions and `doWork` job in `README.md`.
- Changed
  - Replace 'Arduino Zero (USB)' (`zerousb`) board with 'SAMD21 M0-Mini' (`samd21_m0_mini`).
  - For Adafruit Feather M0 LoRa board, change `lmic_pins.rssi_cal` from 10 to 8.
  - For BSFrance LoRa32u4 II board, change `lmic_pins.rssi_cal` from 10 to 8.
  - Set Tx indicators off at `EV_JOINED`, `EV_JOIN_TXCOMPLETE` and `EV_TXCANCELLED`.
  - Change Raspberry Pi Platform (GitHub URL) to official release (name, no URL).
  - Remove `#include <Arduino.h>` from LMIC-node.cpp.
- Fixed
  - Do not schedule uplinks while still joining.  
  `processWork()` will be skipped when still joining (counter will not be read).
  - Incorrect DIO1 pin mapping (5 -> 6) for Adafruit Feather M0 LoRa board.
  - Incorrect #if statement for `LMIC_setDrTxpow()` in `initLmic()`.
  - AU915 joining fails because proper subband is not selected.
  - LMIC_PRINTF_TO not working (properly) (at least on Windows) for boards with ARM based MCU.
  - LMIC_PRINTF_TO not working for boards using SerialUSB.
- Known issues
  - None.

**Release v1.2.0**

- Added
  - Support for Raspberry Pi Pico board.
  - Support for Teensy LC board.
  - New [pinout diagrams](https://github.com/lnlp/pinout-diagrams) repository.
  - Link to pinout diagrams in `README.md`.
  - Links to forum topics in `README.md`.
  - Example output for serial monitor in `README.md`.
  - Improvements in `README.md`.
  - Specify more version numbers for supported boards in `README.md` and platformio.ini.
  - Compile error when `USE_LED` is defined for TTGO T-Beam v1.x boards.
- Changed
  - Prefix BSF file names with `bsf_`.
  - Rename board-id `ttgo_tbeam` to `ttgo_t_beam`.
  - Rename board-id `ttgo_tbeam_v1` to `ttgo_t_beam_v1`.
  - Rename header guards in BSF files that slipped a previous rename action.
  - Order of some chapters in `README.md`.
- Fixed
  - Casing in `#include "LMIC-node.h"` statement in .cpp and BSF files.
- Known issues
  - LMIC debug output currently does not work with Arduino Zero (USB) and Raspberry Pi Pico boards.

**Release v1.1.0 - Maintenance release**

- Update `README.md` and add Release History.
- Add support for SX1276 Low port and SX1272 in RSSI calculation.
- Add LMIC library and LMIC debug level (if >0) to print output.
- Add option to make possible to override in `platformio.ini`, the value of `STM32_POST_INITSERIAL_DELAY_MS` defined in BSF of STM32 boards.
- Add compile error when ABP is used with Classic LMIC because not compliant, generates downlink message for every uplink message because it does not properly handle MAC commands.
- For STM32 BSF's surround postInitSerial delay with `#ifdef USE_SERIAL`.
- In Adafruit Feather M0 LoRa BSF change DIO1 from pin 5 to pin 6 because that is what Adafruit instructs in their tutorial.
- Fix `ABP_DEVICEID` not being used if defined in `lorawan-keys.h`.
- Fix offset for RSSI calculation when using MCCI LMIC.
- Fix printEvent() error when no `USE_DISPLAY` and no `USE_SERIAL` are defined.
- Known issue: The MCCI LoRaWAN LMIC library has a problem with SerialUSB on the Arduino Zero (USB) board so LMIC debug output cannot be used.

**Release v1.0.0 - Initial release**

- First release of LMIC-node.

---

Copyright (c) 2021 Leonel Lopes Parente

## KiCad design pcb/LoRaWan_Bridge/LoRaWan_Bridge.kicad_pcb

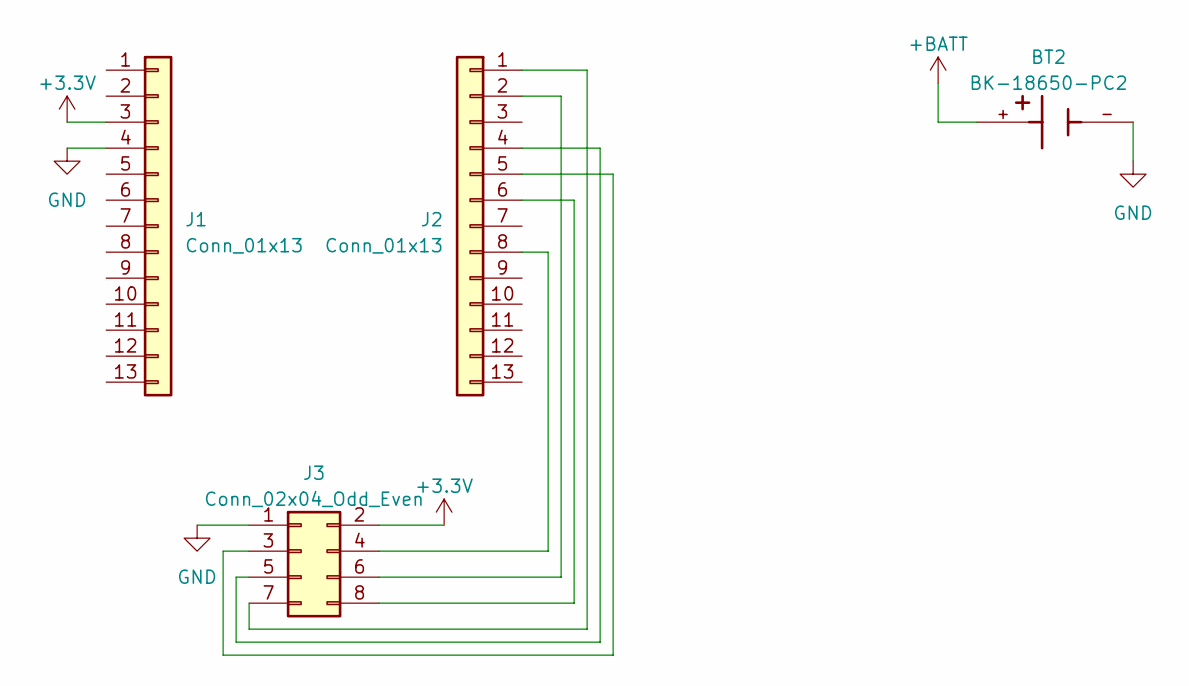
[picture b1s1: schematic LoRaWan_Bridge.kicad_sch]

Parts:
BT2: BK-18650-PC2; BAT_BK-18650-PC2; PARTREV F
J1, J2: Conn_01x13; PinSocket_1x13_P2.54mm_Vertical
J3: Conn_02x04_Odd_Even; PinSocket_2x04_P2.54mm_Vertical

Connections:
+3.3V: J1.3, J3.2
+BATT: BT2.+
GND: BT2.-, J1.4, J3.1
unnamed: J2.1, J3.7
unnamed: J2.2, J3.6
unnamed: J2.4, J3.5
unnamed: J2.5, J3.3
unnamed: J2.6, J3.8
unnamed: J2.8, J3.4

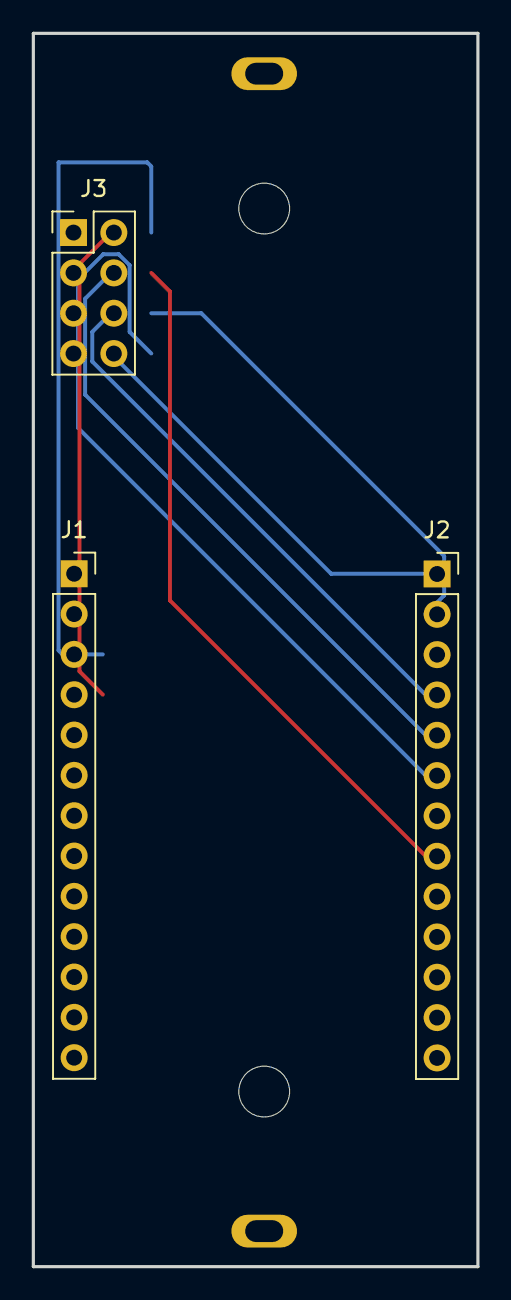
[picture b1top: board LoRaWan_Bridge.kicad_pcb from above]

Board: 2 copper layers, 28.0 x 77.7 mm, 4 parts (1 on the bottom side), 8 nets.

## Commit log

2023-05-15 Readme updates
2023-05-15 Update README.md with pictures
2023-05-15 Update README.md with connection chart
2023-06-08 Add draft PCB
2023-06-18 Updated PCB with correct pin spacing.
2023-06-18 PCB updates to fix pin spacing

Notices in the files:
README.md:
Copyright (c) 2021 Leonel Lopes Parente
